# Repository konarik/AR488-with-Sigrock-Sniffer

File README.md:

# AR488 with Sigrock Sniffer

Combination of [Artgodwin](https://github.com/artgodwin) [Sigrock sniffer](https://github.com/artgodwin/Sigrok-sniffer) and [AR488](https://github.com/artgodwin/AR488-32u4-PCB) with SN7516x design from https://www.eevblog.com/forum/projects/ar488-arduino-based-gpib-adapter/msg4448758/#msg4448758

### NOT TESTED

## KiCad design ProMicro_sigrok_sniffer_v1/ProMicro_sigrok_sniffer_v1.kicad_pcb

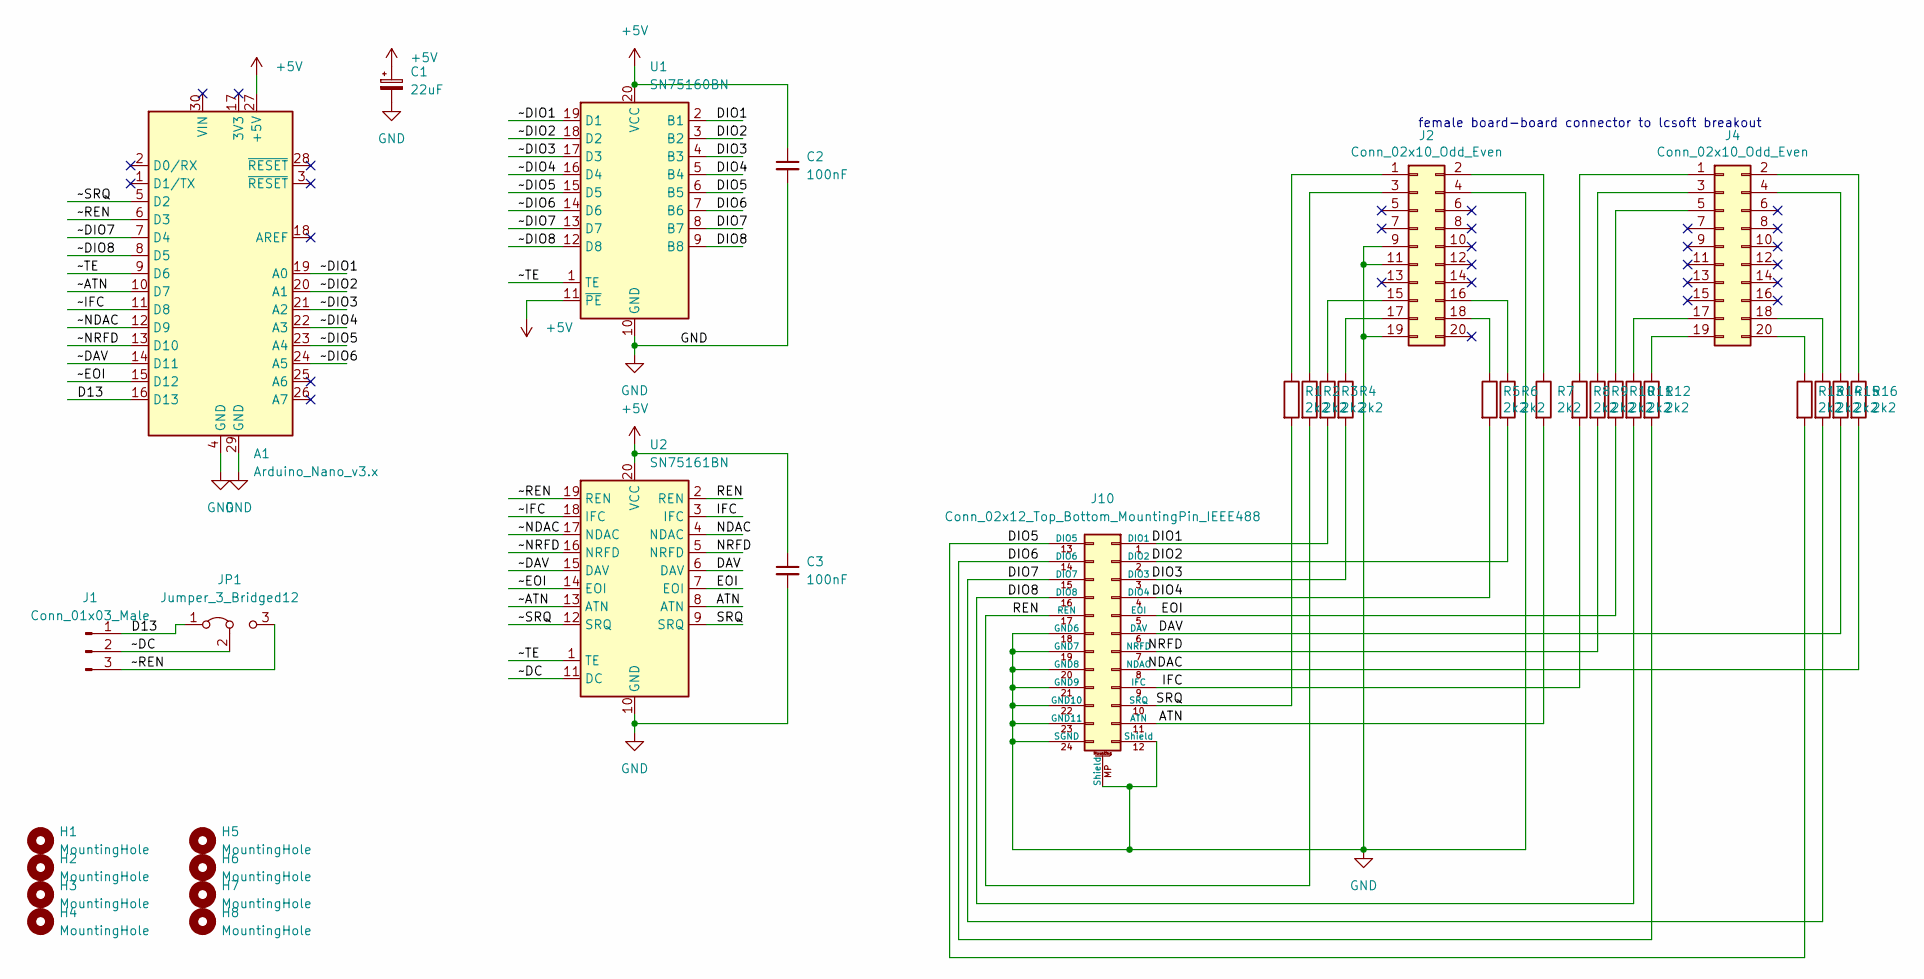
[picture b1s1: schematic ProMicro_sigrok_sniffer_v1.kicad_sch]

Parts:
A1: Arduino_Nano_v3.x; Arduino_Nano
C1: 22uF; CP_Radial_D10.0mm_P2.50mm_P5.00mm_SMD
C2, C3: 100nF; SMD 1206 + C_Rect_L10.0mm_W5.0mm_P5.00mm_P7.50mm
H1, H2, H3, H4, H5, H6, H7, H8: MountingHole; MountingHole_3.5mm
J1: Conn_01x03_Male; PinHeader_1x03_P2.54mm_Vertical
J2, J4: Conn_02x10_Odd_Even; PinSocket_2x10_P2.54mm_Vertical
J10: Conn_02x12_Top_Bottom_MountingPin_IEEE488; Microribbon-24_RA_Male_GPIB
JP1: Jumper_3_Bridged12; SolderJumper-3_P1.3mm_Bridged12_RoundedPad1.0x1.5mm
R1, R2, R3, R4, R5, R6, R7, R8, R9, R10, R11, R12, R13, R14, R15, R16: 2k2; R_1206_3216Metric_Pad1.30x1.75mm_HandSolder
U1: SN75160BN; DIP-20_W7.62mm
U2: SN75161BN; DIP-20_W7.62mm

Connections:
+5V: A1.27 (+5V), C1.1, C2.1, C3.1, U1.11 (~PE), U1.20 (VCC), U2.20 (VCC)
/ATN: J10.11 (ATN), R7.2, U2.8 (ATN)
/D13: A1.16 (D13), J1.1, JP1.1 (A)
/DAV: J10.6 (DAV), R15.2, U2.6 (DAV)
/DIO1: J10.1 (DIO1), R3.2, U1.2 (B1)
/DIO2: J10.2 (DIO2), R6.2, U1.3 (B2)
/DIO3: J10.3 (DIO3), R4.2, U1.4 (B3)
/DIO4: J10.4 (DIO4), R5.2, U1.5 (B4)
/DIO5: J10.13 (DIO5), R13.2, U1.6 (B5)
/DIO6: J10.14 (DIO6), R12.2, U1.7 (B6)
/DIO7: J10.15 (DIO7), R14.2, U1.8 (B7)
/DIO8: J10.16 (DIO8), R11.2, U1.9 (B8)
/EOI: J10.5 (EOI), R10.2, U2.7 (EOI)
/IFC: J10.9 (IFC), R8.2, U2.3 (IFC)
/NDAC: J10.8 (NDAC), R16.2, U2.4 (NDAC)
/NRFD: J10.7 (NRFD), R9.2, U2.5 (NRFD)
/REN: J10.17 (REN), R2.2, U2.2 (REN)
/SRQ: J10.10 (SRQ), R1.2, U2.9 (SRQ)
/~ATN: A1.10 (D7), U2.13 (ATN)
/~DAV: A1.14 (D11), U2.15 (DAV)
/~DC: J1.2, JP1.2 (C), U2.11 (DC)
/~DIO1: A1.19 (A0), U1.19 (D1)
/~DIO2: A1.20 (A1), U1.18 (D2)
/~DIO3: A1.21 (A2), U1.17 (D3)
/~DIO4: A1.22 (A3), U1.16 (D4)
/~DIO5: A1.23 (A4), U1.15 (D5)
/~DIO6: A1.24 (A5), U1.14 (D6)
/~DIO7: A1.7 (D4), U1.13 (D7)
/~DIO8: A1.8 (D5), U1.12 (D8)
/~EOI: A1.15 (D12), U2.14 (EOI)
/~IFC: A1.11 (D8), U2.18 (IFC)
/~NDAC: A1.12 (D9), U2.17 (NDAC)
/~NRFD: A1.13 (D10), U2.16 (NRFD)
/~REN: A1.6 (D3), J1.3, JP1.3 (B), U2.19 (REN)
/~SRQ: A1.5 (D2), U2.12 (SRQ)
/~TE: A1.9 (D6), U1.1 (TE), U2.1 (TE)
GND: A1.4 (GND), A1.29 (GND), C1.2, C2.2, C3.2, J2.4, J2.9, J2.11, J2.19, J10.12 (Shield), J10.18 (GND6), J10.19 (GND7), J10.20 (GND8), J10.21 (GND9), J10.22 (GND10), J10.23 (GND11), J10.24 (SGND), J10.MP (Shield), U1.10 (GND), U2.10 (GND)
unnamed: J2.1, R1.1
unnamed: J2.2, R7.1
unnamed: J2.3, R2.1
unnamed: J2.15, R3.1
unnamed: J2.16, R6.1
unnamed: J2.17, R4.1
unnamed: J2.18, R5.1
unnamed: J4.1, R8.1
unnamed: J4.2, R16.1
unnamed: J4.3, R9.1
unnamed: J4.4, R15.1
unnamed: J4.5, R10.1
unnamed: J4.17, R11.1
unnamed: J4.18, R14.1
unnamed: J4.19, R12.1
unnamed: J4.20, R13.1

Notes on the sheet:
female board-board connector to lcsoft breakout

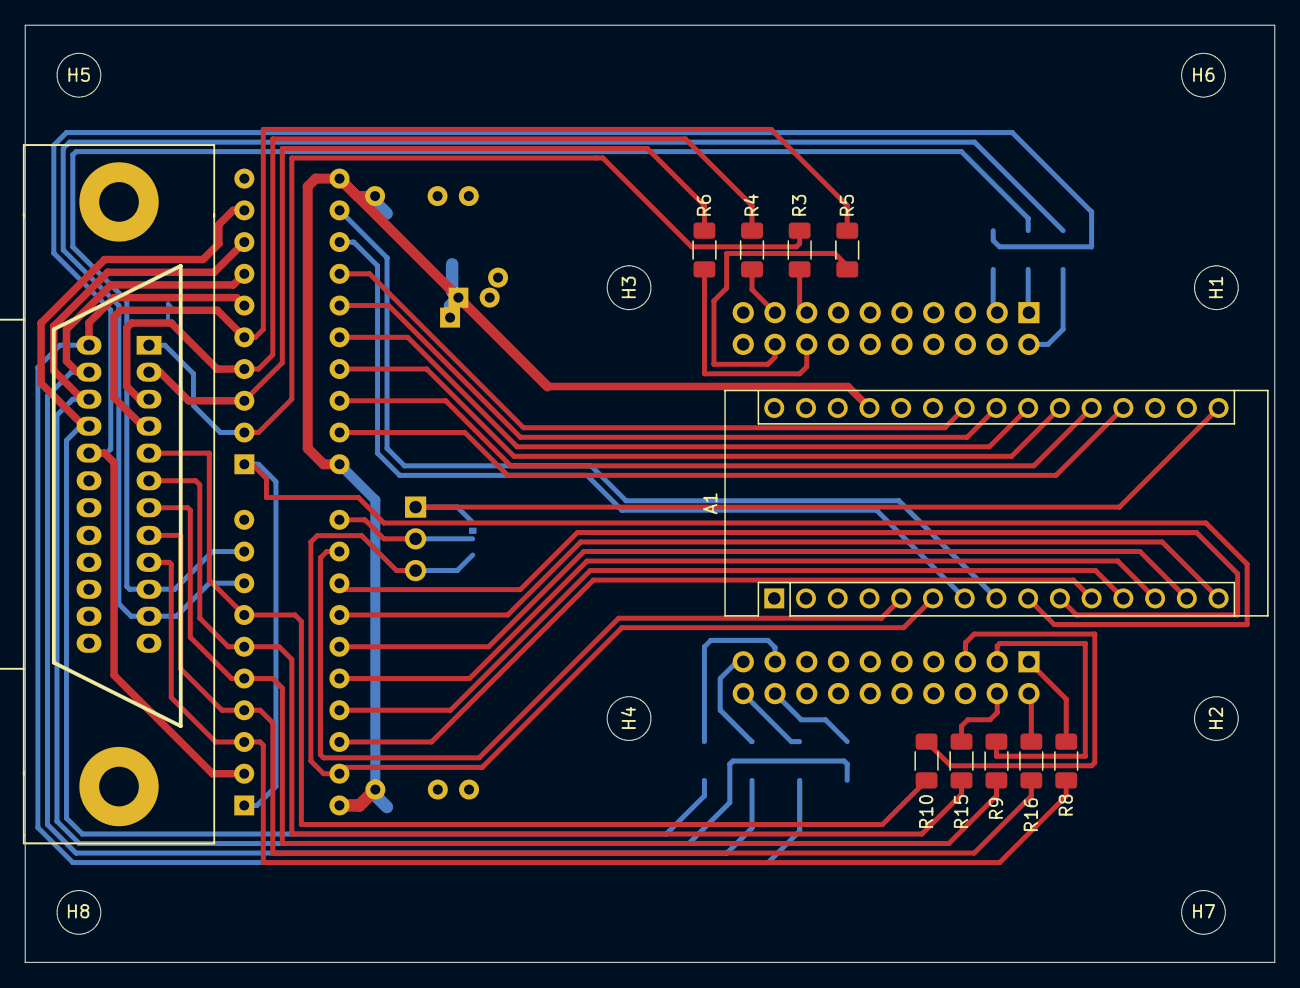
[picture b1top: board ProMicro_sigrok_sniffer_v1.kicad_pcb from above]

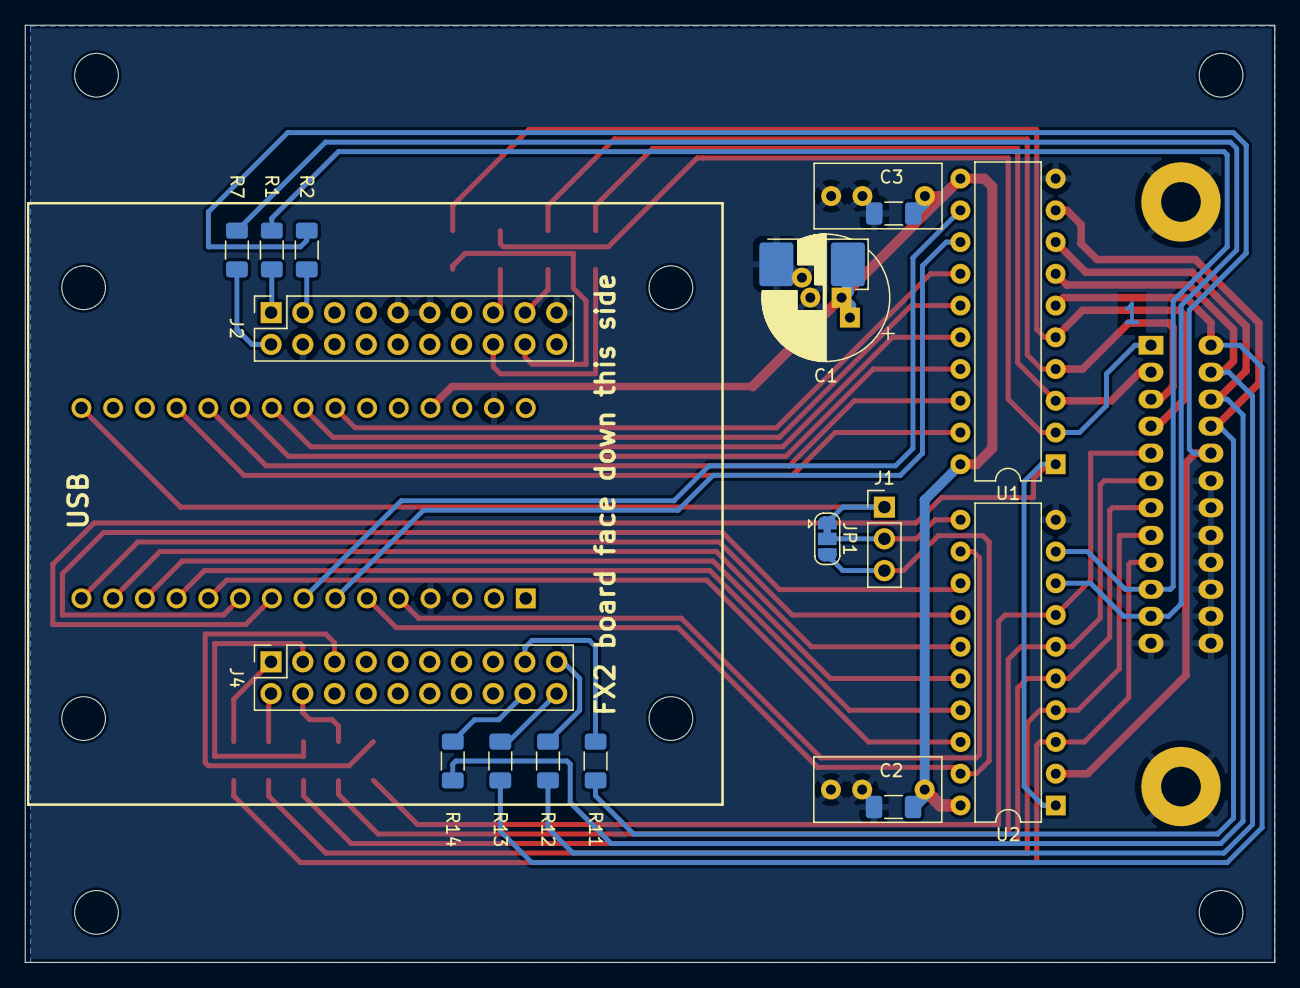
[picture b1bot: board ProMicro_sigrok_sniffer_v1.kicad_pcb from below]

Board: 2 copper layers, 100.0 x 75.0 mm, 35 parts (16 on the bottom side), 53 nets.
